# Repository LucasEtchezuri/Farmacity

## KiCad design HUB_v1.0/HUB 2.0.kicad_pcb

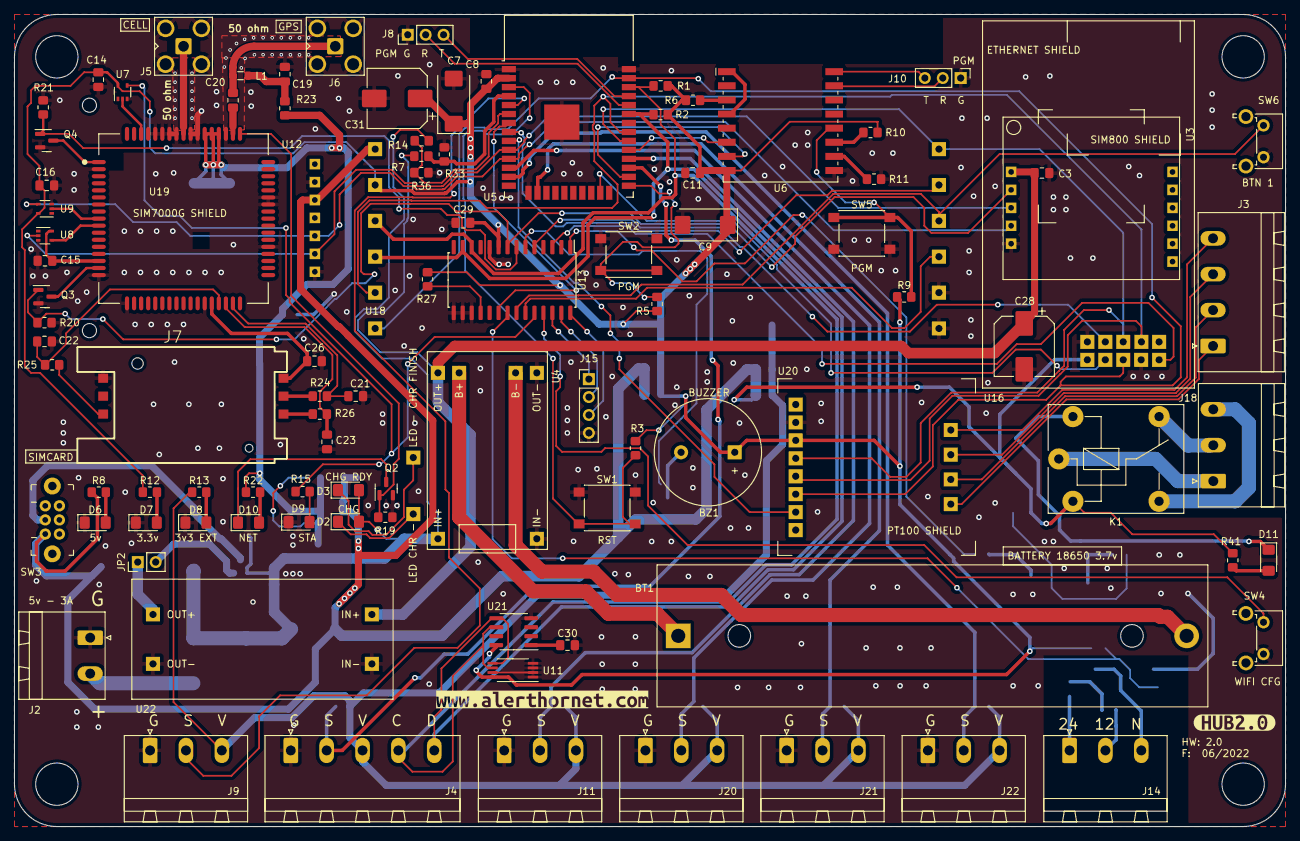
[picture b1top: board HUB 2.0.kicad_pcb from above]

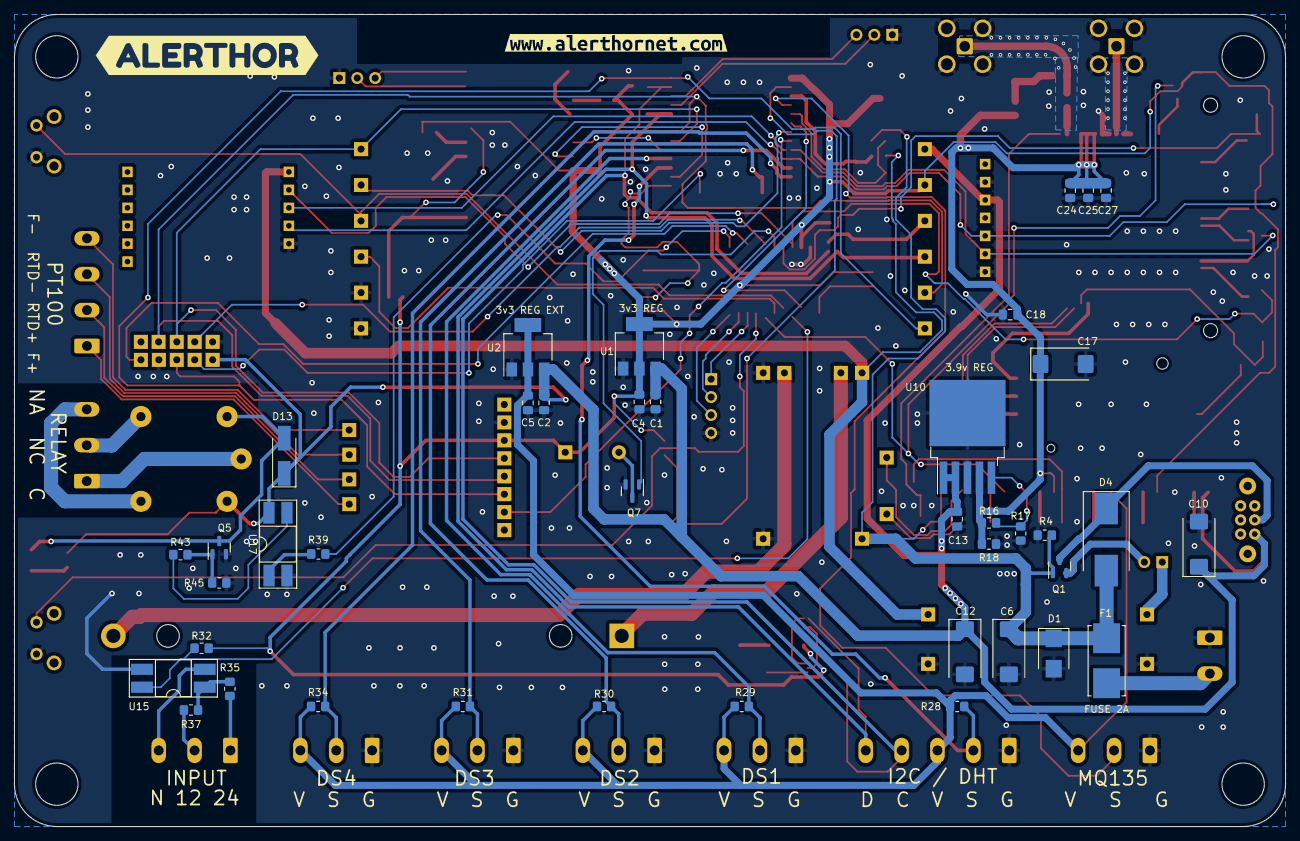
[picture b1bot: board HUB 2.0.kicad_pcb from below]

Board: 2 copper layers, 180.0 x 115.0 mm, 142 parts (42 on the bottom side), 105 nets.

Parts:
BT1: Battery_Cell; BatteryHolder_MPD_BH-18650-PC2
BZ1: Buzzer; Buzzer_15x7.5RM7.6
C1, C2, C4, C5, C30: 10uf; C_0805_2012Metric_Pad1.18x1.45mm_HandSolder
C3, C13, C24: 1uF; C_0805_2012Metric_Pad1.18x1.45mm_HandSolder
C6, C10, C12, C17: 220uf; CP_EIA-7343-31_Kemet-D_Pad2.25x2.55mm_HandSolder
C7, C9: 100uf; CP_EIA-7343-31_Kemet-D_Pad2.25x2.55mm_HandSolder
C8, C11, C14, C15, C16, C18, C25, C26, C29: 100nf; C_0805_2012Metric_Pad1.18x1.45mm_HandSolder
C19, C20, C21, C22, C23, C27: 47pf; C_0805_2012Metric_Pad1.18x1.45mm_HandSolder
C28, C31: 470uf; CP_Elec_8x10
D1: SM6T6V8A; D_SMB
D2, D9: LED ROJO; LED_1206_3216Metric_Pad1.42x1.75mm_HandSolder
D3, D6, D7, D8, D10, D11: LED VERDE; LED_1206_3216Metric_Pad1.42x1.75mm_HandSolder
D4: SK54; D_SMC_Handsoldering
D13: M7; D_SMA_Handsoldering
F1: Fuse; Fuseholder_Littelfuse_Nano2_154x
J2: Conn_01x02_Male; PhoenixContact_MSTBA_2,5_2-G-5,08_1x02_P5.08mm_Horizontal
J3: Conn_01x04_Male; PhoenixContact_MSTBA_2,5_4-G-5,08_1x04_P5.08mm_Horizontal
J4: Conn_01x05_Male; PhoenixContact_MSTBA_2,5_5-G-5,08_1x05_P5.08mm_Horizontal
J5, J6: Conn_Coaxial; SMA_Amphenol_901-143_Horizontal
J7: SIM5060-6-0-26-01-X_REVC; GCT_SIM5060-6-0-26-01-X_REVC
J8, J10: Conn_01x03_Male; PinHeader_1x03_P2.54mm_Vertical
J9, J11, J14, J18, J20, J21, J22: Conn_01x03_Male; PhoenixContact_MSTBA_2,5_3-G-5,08_1x03_P5.08mm_Horizontal
J15: Conn_01x04_Male; PinHeader_1x04_P2.54mm_Vertical
JP2: Jumper_2_Open; PinHeader_1x02_P2.54mm_Vertical
K1: FINDER-36.11; Relay_SPDT_Finder_36.11
L1: 47nh; L_0805_2012Metric
Q1: IRLML6401; SOT-23
Q2, Q3, Q4: DMG2302U; SOT-23
Q5, Q7: 2N7002; SOT-23
R1, R2, R7, R28, R29, R30, R31, R34, R36: 4.7k; R_0805_2012Metric_Pad1.20x1.40mm_HandSolder
R3, R4, R5, R6, R9, R10, R11, R19, R20, R21, R27, R32, R33, R45: 10k; R_0805_2012Metric_Pad1.20x1.40mm_HandSolder
R8: 220; R_0805_2012Metric_Pad1.20x1.40mm_HandSolder
R12, R13: 56; R_0805_2012Metric_Pad1.20x1.40mm_HandSolder
R14: 5,6k; R_0805_2012Metric_Pad1.20x1.40mm_HandSolder
R15, R22: 330; R_0805_2012Metric_Pad1.20x1.40mm_HandSolder
R16: 100k; R_0805_2012Metric_Pad1.20x1.40mm_HandSolder
R17: 47k; R_0805_2012Metric_Pad1.20x1.40mm_HandSolder
R18: 470; R_0805_2012Metric_Pad1.20x1.40mm_HandSolder
R23: 10; R_0805_2012Metric_Pad1.20x1.40mm_HandSolder
R24, R25, R26: 22; R_0805_2012Metric_Pad1.20x1.40mm_HandSolder
R35: 1.2k; R_0805_2012Metric_Pad1.20x1.40mm_HandSolder
R37: 540; R_0805_2012Metric_Pad1.20x1.40mm_HandSolder
R39: 100; R_0805_2012Metric_Pad1.20x1.40mm_HandSolder
R41: 180; R_0805_2012Metric_Pad1.20x1.40mm_HandSolder
R43: 1k; R_0805_2012Metric_Pad1.20x1.40mm_HandSolder
SW1, SW2, SW5: SW_Push; SW_Push_1P1T_NO_6x6mm_H9.5mm
SW3: SW_DPDT_x2; EG2211
SW4, SW6: SW_Push; SW_Tactile_SPST_Angled_PTS645Vx39-2LFS
U1, U2: AP1117-33; SOT-223-3_TabPin2
U3: SIM800L-MODULE; SIM800L_MODULE
U4: TP4056_MOD_LEDS
U5: ESP32-WROOM-32D; ESP32-WROOM-32
U6: ESP-07
U7, U8, U9: SN74LV1T34DCK; SOT-353_SC-70-5
U10: MIC29302WU; TO-263-5_TabPin3
U11: 24LC512; TSSOP-8_4.4x3mm_P0.65mm
U12: SIM7000; SIMCON_SIM7000E
U13: MCP23017_SO; SOIC-28W_7.5x17.9mm_P1.27mm
U15, U17: PC817; DIP-4_W8.89mm_SMDSocket_LongPads
U16: Funduino; Ethernet Funduino
U18: Display Module 01 Alerthor; Display Module Alerthor
U19: SIM7000G_MODULE
U20: MAX3186_MODULE
U21: 47L16; SOIC-8_3.9x4.9mm_P1.27mm
U22: MT3608 MODULE; MT3608_MOD
kibuzzard-626AF3F8: G***; kibuzzard-626AF3F8
kibuzzard-626AF556: G***; kibuzzard-626AF556
kibuzzard-626AF666: G***; kibuzzard-626AF666
kibuzzard-626862BC: G***; kibuzzard-626862BC

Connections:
3v3_EXT: C5.1, J4.3, J9.3, J11.3, J20.3, J21.3, J22.3, R13.1, R28.2, R29.2, R30.2, R31.2, R34.2, U2.2 (VO)
+3V3: BZ1.1 (-), C4.1, C7.1, C8.1, C9.1, C11.1, C14.2, C16.2, C29.1, C31.1, R1.1, R2.1, R3.1, R5.1, R6.2, R9.1, R10.1, R12.1, R27.1, R32.1, U1.2 (VO), U5.2 (VDD), U6.8 (VCC), U7.5 (VCC), U9.5 (VCC), U11.8 (VCC), U13.9 (VDD), U18.2 (VCC_3.3v), U20.3 (3V3), U21.8 (VCC)
+5V: C1.1, C2.1, C10.1, C12.1, C13.1, D13.1 (K), K1.A1, R8.1, R41.1, SW3.1 (A), U1.3 (VI), U2.3 (VI), U10.1 (EN), U10.2 (VIN), U16.10 (VCC), U17.4, U18.1 (VCC_5v), U19.5 (VCC_5V)
+5VL: C6.1, D1.1 (A1), D2.2 (A), D3.2 (A), D4.2 (A), F1.2, Q1.1 (G), R4.1, R14.1, U4.2 (VCC)
+BATT: C3.1, C28.1, R7.1, U3.11 (VCC), U4.3 (OUT_+), U22.2 (IN_+)
A: U6.1 (~RST), U6.4 (GPIO16)
BUZZER: Q7.1 (G), U13.6 (GPB5)
DHT: J4.2, R28.1, U5.27 (IO16)
DS1: J11.2, R29.1, U5.28 (IO17)
DS2: J20.2, R30.1, U5.12 (IO27)
DS3: J21.2, R31.1, U5.16 (IO13)
DS4: J22.2, R34.1, U5.13 (IO14)
E1: R32.2, U13.21 (GPA0), U15.4
ETH_RST: U13.5 (GPB4), U16.7 (RST)
GND: C1.2, C2.2, C3.2, C4.2, C5.2, C6.2, C7.2, C8.2, C9.2, C10.2, C11.2, C12.2, C13.2, C14.1, C15.1, C16.1, C17.2, C18.2, C19.2, C21.2, C22.2, C23.2, C24.2, C25.2, C26.2, C27.2, C28.2, C29.2, C30.2, C31.2, D1.2 (A2), D6.1 (K), D7.1 (K), D8.1 (K), D9.1 (K), J2.1, J4.1, J5.2 (Ext), J6.2 (Ext), J7.C5 (GND), J8.1, J9.1, J10.1, J11.1, J15.4, J20.1, J21.1, J22.1, Q2.2 (S), Q3.2 (S), Q4.2 (S), Q5.2 (S), Q7.2 (S), R4.2, R11.1, R17.1, R18.1, R19.1, R20.1, R21.1, R33.2, R36.2, R45.2, SW1.1, SW2.1, SW4.2, SW5.2, SW6.2, U1.1 (GND), U2.1 (GND), U3.7 (GND), U4.1 (GND), U5.1 (GND), U5.15 (GND), U5.38 (GND), U5.39 (GND), U6.9 (GND), U7.3 (GND), U8.3 (GND), U9.3 (GND), U10.3 (GND), U11.1 (A0), U11.2 (A1), U11.3 (A2), U11.4 (GND), U11.7 (WP), U12.2 (GND), U12.17 (GND), U12.18 (GND), U12.29 (GND), U12.39 (GND), U12.45 (GND), U12.46 (GND), U12.54 (GND), U12.58 (GND), U12.59 (GND), U12.61 (GND), U12.62 (GND), U12.63 (GND), U12.64 (GND), U12.65 (GND), U13.10 (VSS), U13.15 (A0), U13.16 (A1), U13.17 (A2), U15.3, U16.4 (GND), U16.9 (GND), U17.2, U18.11 (GND), U18.12 (GND), U19.1 (GND), U19.6 (GND), U20.2 (GND), U21.4 (VSS), U22.1 (GND)
GPA5: J15.1, U13.26 (GPA5)
GPA6: J15.2, U13.27 (GPA6)
GPA7: J15.3, U13.28 (GPA7)
INTA: U5.7 (IO35), U13.20 (INTA)
InterUc_RX: U5.26 (IO4), U6.7 (GPIO13)
InterUc_TX: U5.29 (IO5), U6.6 (GPIO12)
MDM_GNSS_ANT: C20.2, U12.53 (GNSS_ANT)
MDM_NETLIGHT: Q2.1 (G), R19.2, U12.52 (NETLIGHT)
MDM_PWRKEY: Q4.3 (D), U12.1 (~PWRKEY)
MDM_RESET: Q3.3 (D), U12.16 (~NRESET)
MDM_RX: U8.4 (Y), U12.10 (RXD)
MDM_STATUS: U7.2 (A), U12.66 (STATUS)
MDM_TX: U9.2 (A), U12.9 (TXD)
MQ135: J9.2, U5.5 (SENSOR_VN)
NOW_RX: J10.2, U6.15 (GPIO3/RXD)
NOW_TX: J10.3, U6.16 (GPIO1/TXD)
unnamed: BT1.1 (+), U4.4 (B+)
unnamed: BT1.2 (-), U4.5 (B-)
unnamed: BZ1.2 (+), Q7.3 (D)
unnamed: C19.1, L1.1, R23.2
unnamed: C20.1, J6.1 (In), L1.2
unnamed: C30.1, U21.1 (VCAP)
unnamed: D2.1 (K), U4.6 (LED_CARGA_-)
unnamed: D3.1 (K), U4.7 (LED_FIN_-)
unnamed: D4.1 (K), Q1.3 (D), SW3.2 (B)
unnamed: D6.2 (A), R8.2
unnamed: D7.2 (A), R12.2
unnamed: D8.2 (A), R13.2
unnamed: D9.2 (A), R15.1
unnamed: D10.1 (K), Q2.3 (D)
unnamed: D10.2 (A), R22.2
unnamed: D11.1 (K), D13.2 (A), K1.A2, Q5.3 (D)
unnamed: D11.2 (A), R41.2
unnamed: F1.1, J2.2
unnamed: J3.1, U20.12 (F+)
unnamed: J3.2, U20.11 (RTD+)
unnamed: J3.3, U20.10 (RTD-)
unnamed: J3.4, U20.9 (F-)
unnamed: J5.1 (In), U12.60 (RF_ANT)
unnamed: J7.C2 (RST), R24.2
unnamed: J7.C3 (CLK), R26.2
unnamed: J7.C7 (I/O), R25.2
unnamed: J14.1, R35.1
unnamed: J14.2, R37.1
unnamed: J14.3, U15.2
unnamed: J18.1, K1.11
unnamed: J18.2, K1.12
unnamed: J18.3, K1.14
unnamed: JP2.1 (A), U22.3 (OUT_+)
unnamed: JP2.2 (B), Q1.2 (S)
unnamed: Q5.1 (G), R43.2, R45.1
unnamed: R3.2, SW1.2, U5.3 (EN)
unnamed: R5.2, SW2.2, U5.25 (IO0)
unnamed: R6.1, U6.3 (EN)
unnamed: R9.2, SW5.1, U6.12 (GPIO0)
unnamed: R10.2, U6.11 (GPIO2)
unnamed: R11.2, U6.10 (GPIO15)
unnamed: R14.2, R36.1, U5.6 (IO34)
unnamed: R16.1, R17.2, U10.5 (ADJ)
unnamed: R27.2, U13.18 (~RESET)
unnamed: R7.2, R33.1, U5.4 (SENSOR_VP)
unnamed: R35.2, R37.2, U15.1
unnamed: R39.2, U17.1
unnamed: R43.1, U17.3
S1: R39.1, U13.1 (GPB0)
SCL: J4.4, R1.2, U5.36 (IO22), U11.6 (SCL), U13.12 (SCK), U18.3 (SCL), U21.6 (SCL)
SDA: J4.5, R2.2, U5.33 (IO21), U11.5 (SDA), U13.13 (SDA), U18.4 (SDA), U21.5 (SDA)
SIM7000G_PWRKEY: Q4.1 (G), R21.2, U13.7 (GPB6)
SIM7000G_RESET: Q3.1 (G), R20.2, U3.10 (RST), U13.8 (GPB7)
SIM7000G_RX: U3.8 (TXD), U5.11 (IO26), U9.4 (Y), U19.3 (TX)
SIM7000G_STATUS: R15.2, U7.4 (Y), U13.24 (GPA3)
SIM7000G_TX: U3.9 (RXD), U5.10 (IO25), U8.2 (A), U19.2 (RX)
SIM_CLK: C23.1, R26.1, U12.32 (SIM_CLK)
SIM_DATA: C22.1, R25.1, U12.31 (SIM_DATA)
SIM_RST: C21.1, R24.1, U12.33 (SIM_RST)
SIM_VDD: C26.1, J7.C1 (VCC), U12.30 (SIM_VDD)
SPI_CLK: U5.30 (IO18), U16.5 (CLK), U18.7 (CLK), U20.4 (CLK)
SPI_DISP_CS: U5.8 (IO32), U18.8 (CS)
SPI_ETH_CS: U5.23 (IO15), U16.8 (CS)
SPI_ETH_CS2: U13.3 (GPB2), U16.2 (CS2)
SPI_MISO: U5.31 (IO19), U16.3 (MISO), U18.5 (MISO), U20.5 (SDO)
SPI_MOSI: U5.37 (IO23), U16.6 (MOSI), U18.6 (MOSI), U20.6 (SDI)
SPI_PT100_CS: U5.9 (IO33), U20.7 (CS)
SW1: SW6.1, U13.22 (GPA1), U18.9 (BTN1)
SW2: U13.23 (GPA2), U18.10 (BTN2)
VBAT: C17.1, C18.1, C24.1, C25.1, C27.1, R16.2, R18.2, R22.1, R23.1, U10.4 (VOUT), U12.55 (VBAT), U12.56 (VBAT), U12.57 (VBAT)
VDD_EXT_1.8: C15.2, U8.5 (VCC), U12.15 (VDD_EXT)
WIFI_CFG: SW4.1, U13.25 (GPA4)
uC_RX: J8.2, U5.34 (RXD0/IO3)
uC_TX: J8.3, U5.35 (TXD0/IO1)

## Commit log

2024-02-27 Inicial
2024-02-27 Avanzo en la v2
2024-02-27 Ultimas modificaciones v1
2024-02-27 Revert "Ultimas modificaciones v1"
    This reverts commit 6e79455464ab0dc02e26e3c93cbaf695e8eb9dae.
2024-02-27 agrego archivo
2026-03-15 Add Privacy Policy for Sensiva application
    Added a comprehensive privacy policy detailing data collection, usage, and user rights for the Sensiva application.
2026-03-15 Rename PrivacyPolicy.html to index.html
